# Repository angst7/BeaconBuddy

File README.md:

#BeaconBuddy#

nRF52832 based beacon design

Simple reference design in a 1"x1.2" form factor with CR2032 battery holder.  Rev. A Tested to work with examples from the nRF52 SDK v11.0.0, but no
guarantees as to the effectiveness of the antenna.  

This design is related to the [nRF52Beacon] (https://github.com/angst7/nRF52beacon) project with the addition of A BME280 Sensor for pressure, temperature, 
and humidity readings.  It also breaks out GPIO/AIn pin P0.02.

** Revision History ** 
- Rev. A is tested and working, please clone the rev_a branch for that version.
- 10/22/2016: Rev. B removed ST humidity sensor, replaced BMP280 with BME280, and replaced diode battery polarity protection with a FET.
- 10/23/2016: Rev. C adds a reset button, and second LED
- This is the Rev. C version.  It is not yet tested with real hardware, but should be fine.

##License##

This work is licensed under [CC Attribution 3.0 United States](https://creativecommons.org/licenses/by/3.0/us/).

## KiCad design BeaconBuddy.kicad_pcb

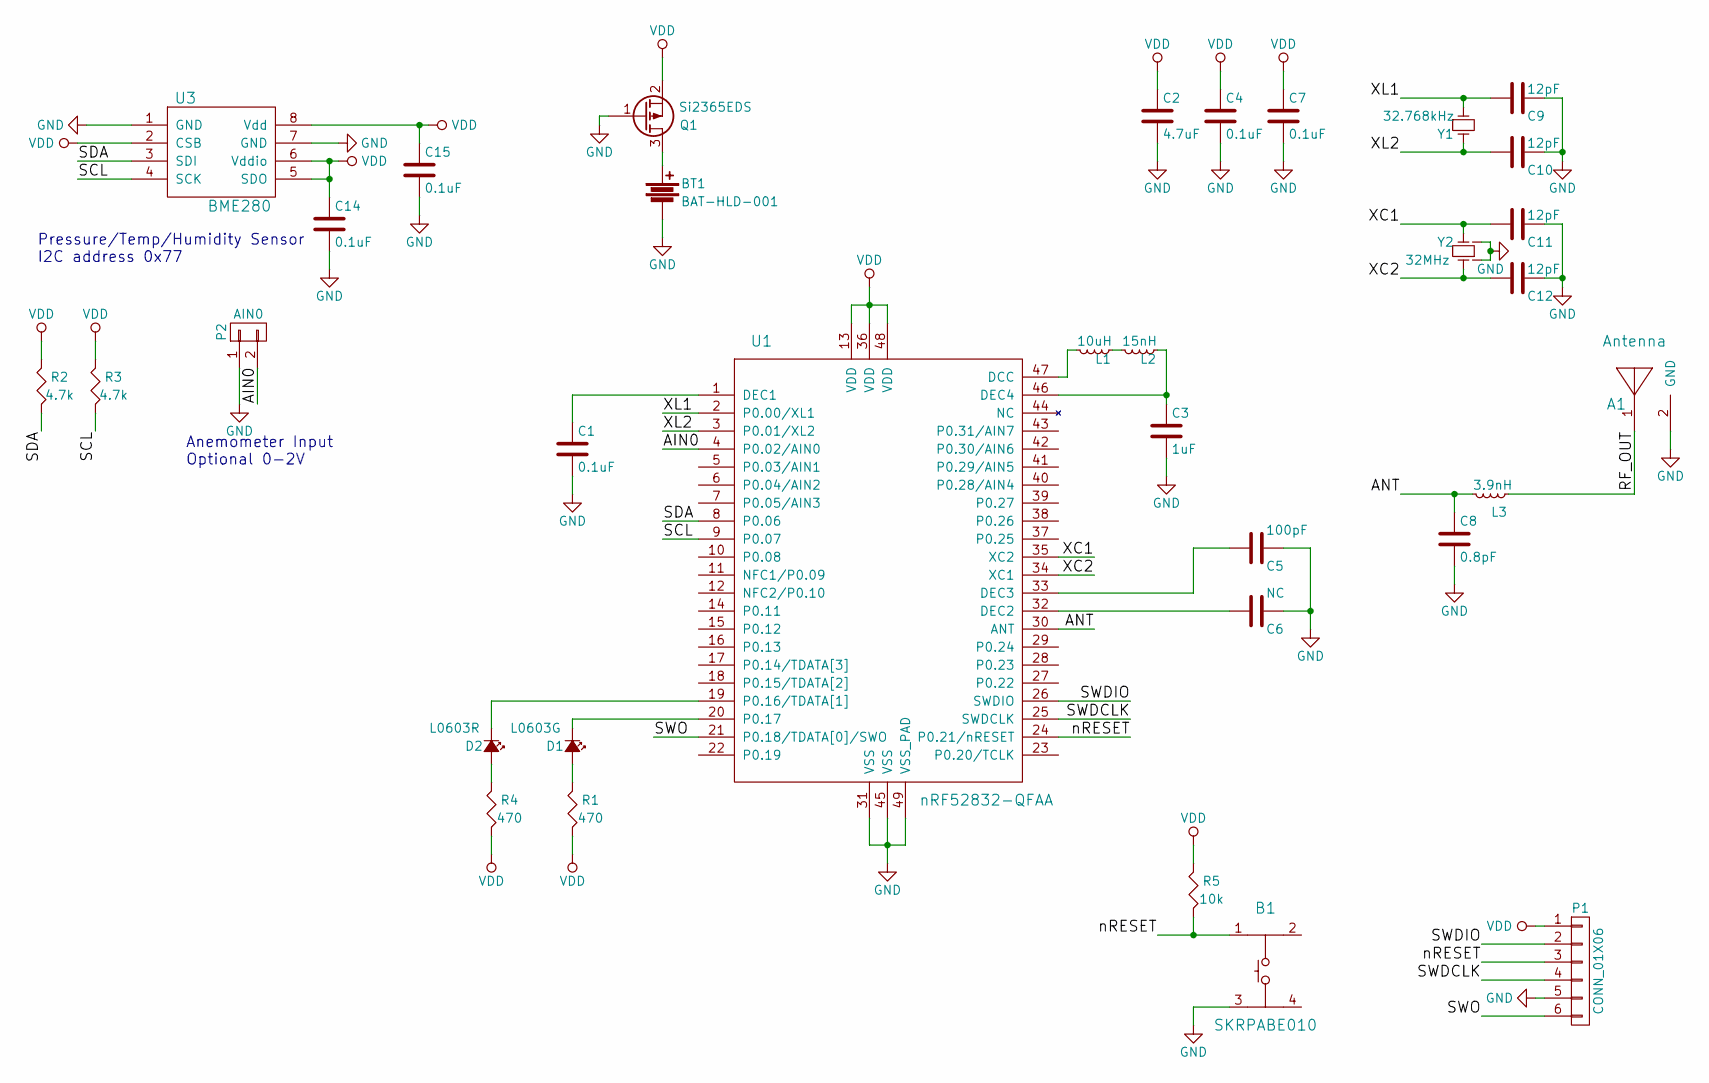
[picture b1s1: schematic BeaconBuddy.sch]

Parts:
A1: Antenna; Antenna-2.45GHZ
B1: SKRPABE010
BT1: BAT-HLD-001; BATT-HLD-001
C1, C4, C7, C14, C15: 0.1uF; C_0603
C2: 4.7uF; C_0603
C3: 1uF; C_0603
C5: 100pF; C_0603
C6: NC; C_0603
C8: 0.8pF; C_0402
C9, C10, C11, C12: 12pF; C_0603
D1: L0603G; LED_0603
D2: L0603R; LED_0603
L1: 10uH; C_0603
L2: 15nH; C_0603
L3: 3.9nH; C_0402
P1: CONN_01X06; TC2030-MCP-NL
P2: AIN0; CONN_100mil_1x2
Q1: Si2365EDS; SOT-23
R1, R4: 470; R_0603
R2, R3: 4.7k; R_0603
R5: 10k; R_0603
U1: nRF52832-QFAA; UQFN-48-1EP_6x6mm_Pitch0.4mm
U3: BME280; Bosch_LGA8_2.5x2.5
Y1: 32.768kHz; Crystal_ABS06
Y2: 32MHz; Crystal_ABM11

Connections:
/AIN0: P2.2, U1.4 (P0.02/AIN0)
/ANT: C8.1, L3.2, U1.30 (ANT)
/RF_OUT: A1.1, L3.1
/SCL: R3.2, U1.9 (P0.07), U3.4 (SCK)
/SDA: R2.2, U1.8 (P0.06), U3.3 (SDI)
/SWDCLK: P1.4, U1.25 (SWDCLK)
/SWDIO: P1.2, U1.26 (SWDIO)
/SWO: P1.6, U1.21 (P0.18/TDATA[0]/SWO)
/XC1: C11.2, U1.35 (XC2), Y2.3
/XC2: C12.2, U1.34 (XC1), Y2.1
/XL1: C9.2, U1.2 (P0.00/XL1), Y1.1
/XL2: C10.2, U1.3 (P0.01/XL2), Y1.2
/nRESET: B1.1, P1.3, R5.2, U1.24 (P0.21/nRESET)
GND: A1.2 (GND), B1.3, BT1.2, C1.2, C2.2, C3.2, C4.2, C5.1, C6.1, C7.2, C8.2, C9.1, C10.1, C11.1, C12.1, C14.2, C15.2, P1.5, P2.1, Q1.1 (G), U1.31 (VSS), U1.45 (VSS), U1.49 (VSS_PAD), U3.1 (GND), U3.7 (GND), Y2.2, Y2.4
unnamed: BT1.1, Q1.3 (D)
unnamed: C1.1, U1.1 (DEC1)
unnamed: C3.1, L2.1, U1.46 (DEC4)
unnamed: C5.2, U1.33 (DEC3)
unnamed: C6.2, U1.32 (DEC2)
unnamed: D1.1 (K), U1.20 (P0.17)
unnamed: D1.2 (A), R1.1
unnamed: D2.1 (K), U1.19 (P0.16/TDATA[1])
unnamed: D2.2 (A), R4.1
unnamed: L1.1, L2.2
unnamed: L1.2, U1.47 (DCC)
VDD: C2.1, C4.1, C7.1, C14.1, C15.1, P1.1, Q1.2 (S), R1.2, R2.1, R3.1, R4.2, R5.1, U1.13 (VDD), U1.36 (VDD), U1.48 (VDD), U3.2 (CSB), U3.5 (SDO), U3.6 (Vddio), U3.8 (Vdd)

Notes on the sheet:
Pressure/Temp/Humidity Sensor I2C address 0x77
Anemometer Input Optional 0-2V

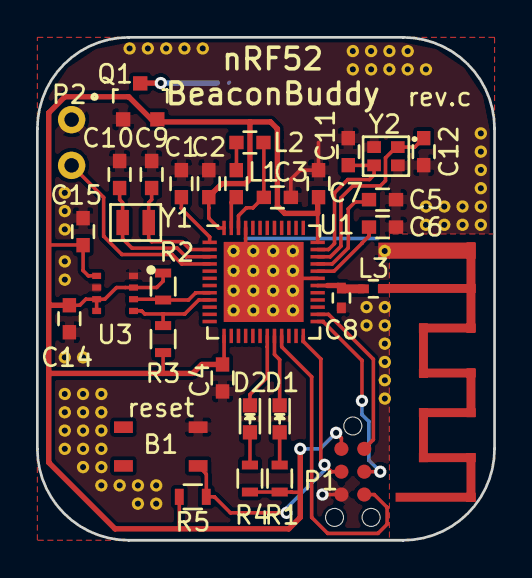
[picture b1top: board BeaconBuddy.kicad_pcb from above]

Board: 2 copper layers, 25.4 x 27.9 mm, 34 parts (1 on the bottom side), 26 nets.

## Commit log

2016-07-16 Inital commit
2016-07-16 Added Temp/Humidity sensor
2016-07-16 Added Pressure Sensor
2016-07-16 Added optional Anemometer/Analog Input
2016-07-17 Fixed ground pin issue:
2016-08-20 Fixed Names
2016-08-20 Updated Silk
2016-08-20 Added Readme
2016-10-23 Switch to PMOS battery protection
2016-10-23 Switch to BME280, update PCB
2016-10-23 Add reset switch, second LED
2016-10-24 Update Readme for rev. C
2016-10-26 Add schematic, image for rev.c
